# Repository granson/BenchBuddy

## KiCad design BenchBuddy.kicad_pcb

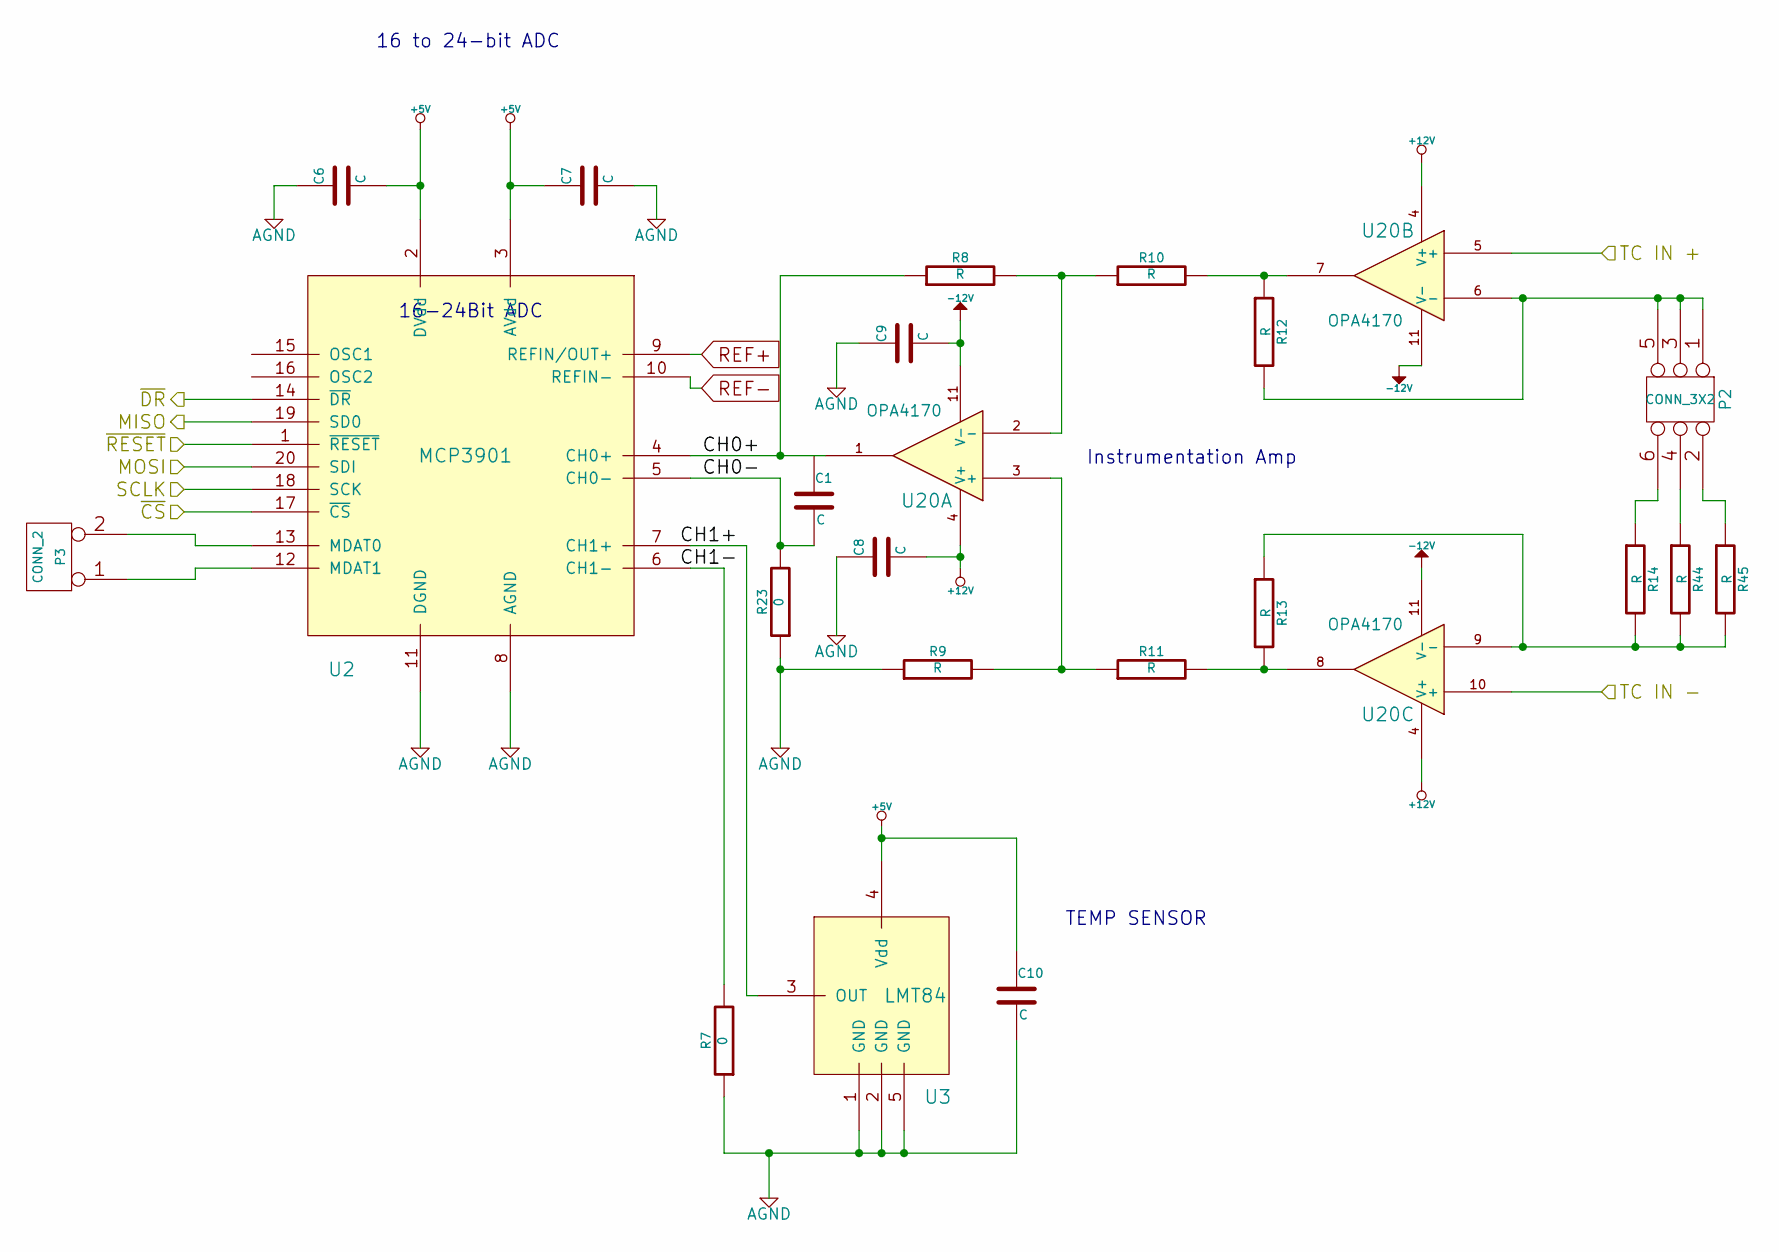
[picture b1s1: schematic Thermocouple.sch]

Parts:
C1, C6, C7, C8, C9, C10: C
P2: CONN_3X2
P3: CONN_2
R7, R23: 0
R8, R9, R10, R11, R12, R13, R14, R44, R45: R
U2: MCP3901
U3: LMT84
U20: OPA4170

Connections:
+5V: C6.2, C7.1, C10.1, U2.2 (DVdd), U2.3 (AVdd), U3.4 (Vdd); also elsewhere on the board
+12V: C8.2, U20.4 (V+); also elsewhere on the board
-12V: C9.2, U20.11 (V-); also elsewhere on the board
/Arduino/MISO: U2.19 (SD0); also elsewhere on the board
/Arduino/MOSI: U2.20 (SDI); also elsewhere on the board
/Arduino/SCLK: U2.18 (SCK); also elsewhere on the board
/Arduino/~ADC_CS: U2.17 (~CS); also elsewhere on the board
/Arduino/~DR: U2.14 (~DR); also elsewhere on the board
/Arduino/~RESET: U2.1 (~RESET); also elsewhere on the board
/Thermocouple/CH0+: R8.1, U2.4 (CH0+), U20.1
/Thermocouple/CH0-: C1.2, R23.2, U2.5 (CH0-)
/Thermocouple/TC IN +: U20.5 (+); also elsewhere on the board
/Thermocouple/TC IN -: U20.10 (+); also elsewhere on the board
AGND: C6.1, C7.2, C8.1, C9.1, C10.2, R7.1, R9.1, R23.1, U2.8 (AGND), U2.11 (DGND), U3.1 (GND), U3.2 (GND), U3.5 (GND); also elsewhere on the board
unnamed: P3.2 (PM), U2.13 (MDAT0)
unnamed: P3.1, U2.12 (MDAT1)
unnamed: P2.1, P2.3, P2.5, R12.2, U20.6 (-)
unnamed: R9.2, R11.1, U20.3 (+)
unnamed: R8.2, R10.1, U20.2 (-)
unnamed: R13.1, R14.2, R44.2, R45.2, U20.9 (-)
unnamed: P2.4, R44.1
unnamed: R7.2, U2.6 (CH1-)
unnamed: R11.2, R13.2, U20.8
unnamed: P2.2, R45.1
unnamed: R10.2, R12.1, U20.7
unnamed: U2.7 (CH1+), U3.3 (OUT)
unnamed: P2.6, R14.1

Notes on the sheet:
TEMP SENSOR
Instrumentation Amp
16-24Bit ADC
16 to 24-bit ADC

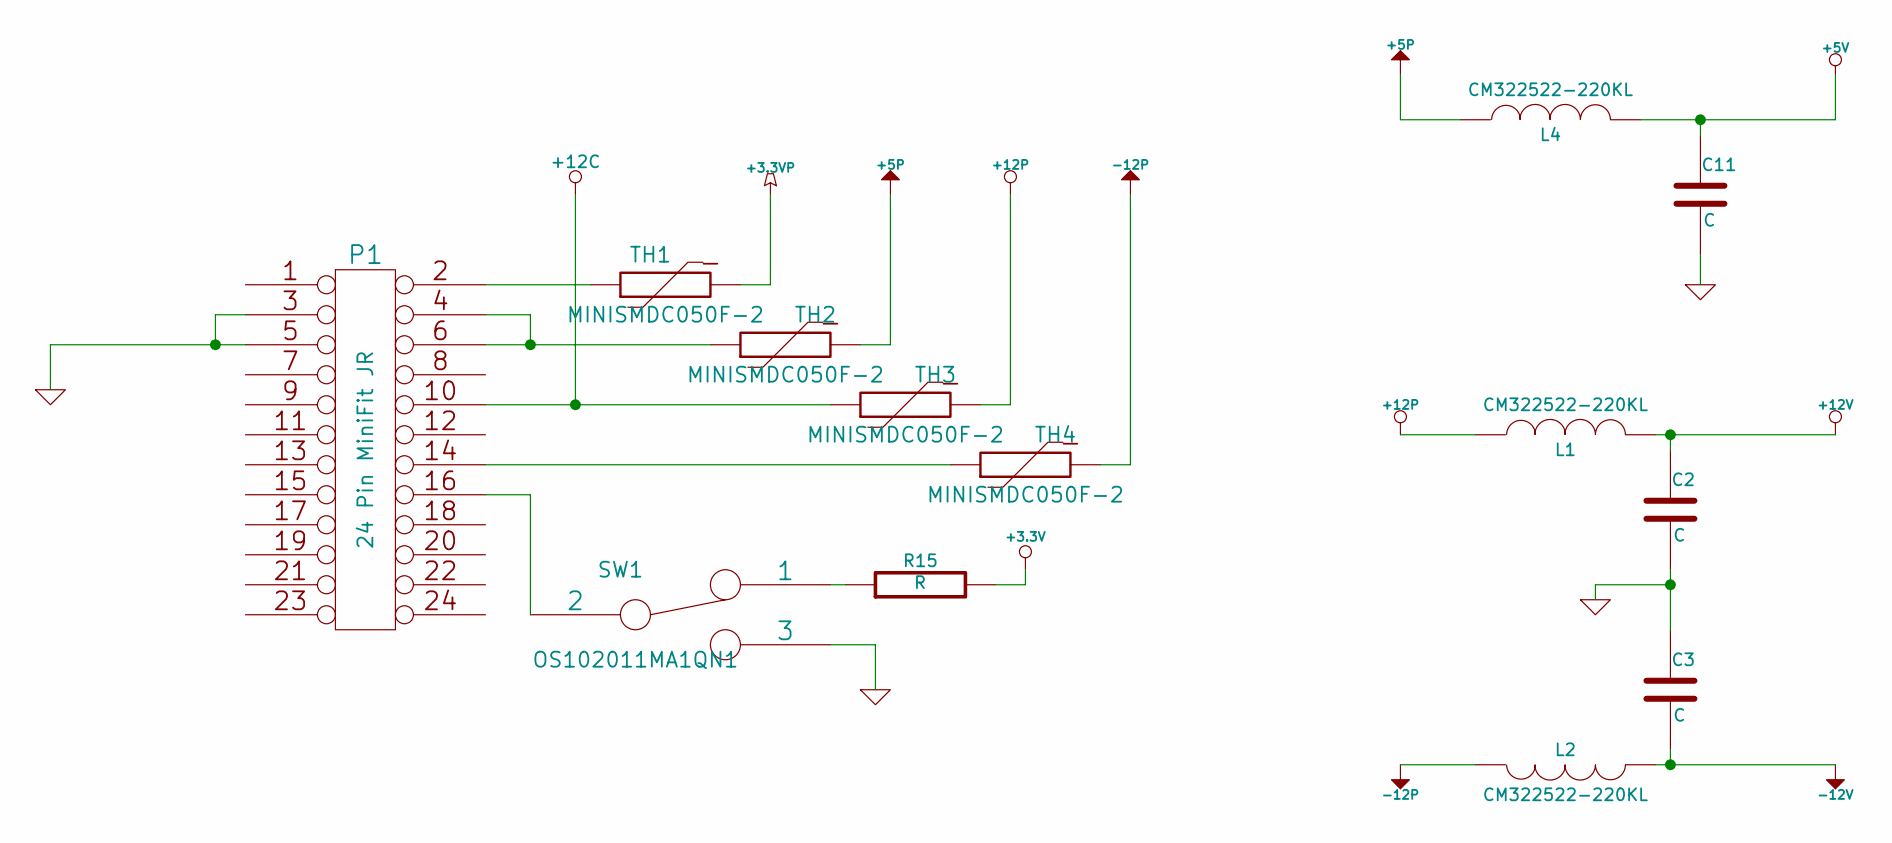
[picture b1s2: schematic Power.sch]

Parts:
C2, C3, C11: C
L1, L2, L4: CM322522-220KL; MFG Part Number CM322522-220KL
P1: 24 Pin MiniFit JR
R15: R
SW1: OS102011MA1QN1; MFG Part Number OS102011MA1QN1
TH1, TH2, TH3, TH4: MINISMDC050F-2; MFG Part Number MINISMDC050F-2

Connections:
+3.3V: R15.2; also elsewhere on the board
+5P: L4.1, TH2.2
+5V: C11.1, L4.2; also elsewhere on the board
+12C: P1.10, TH3.1; also elsewhere on the board
+12P: L1.1, TH3.2; also elsewhere on the board
+12V: C2.1, L1.2; also elsewhere on the board
-12P: L2.1, TH4.2
-12V: C3.2, L2.2; also elsewhere on the board
GND: C2.2, C3.1, C11.2, P1.3, P1.5, SW1.3; also elsewhere on the board
unnamed: R15.1, SW1.1
unnamed: P1.16, SW1.2
unnamed: P1.14, TH4.1
unnamed: P1.2, TH1.1
unnamed: P1.4, P1.6, TH2.1

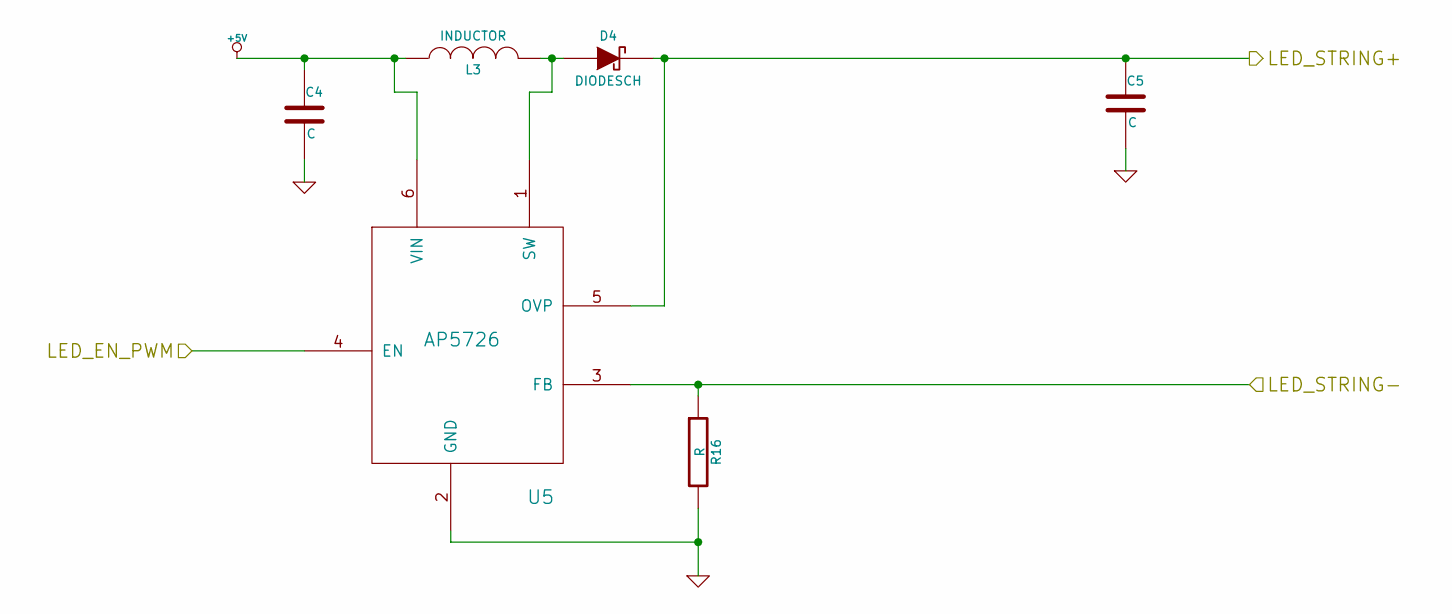
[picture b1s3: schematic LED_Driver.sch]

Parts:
C4, C5: C
D4: DIODESCH
L3: INDUCTOR
R16: R
U5: AP5726

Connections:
+5V: C4.1, L3.1, U5.6 (VIN); also elsewhere on the board
/LED_Driver/LED_STRING+: C5.1, D4.2 (K), U5.5 (OVP); also elsewhere on the board
/LED_Driver/LED_STRING-: R16.1, U5.3 (FB); also elsewhere on the board
GND: C4.2, C5.2, R16.2, U5.2 (GND); also elsewhere on the board
unnamed: D4.1 (A), L3.2, U5.1 (SW)

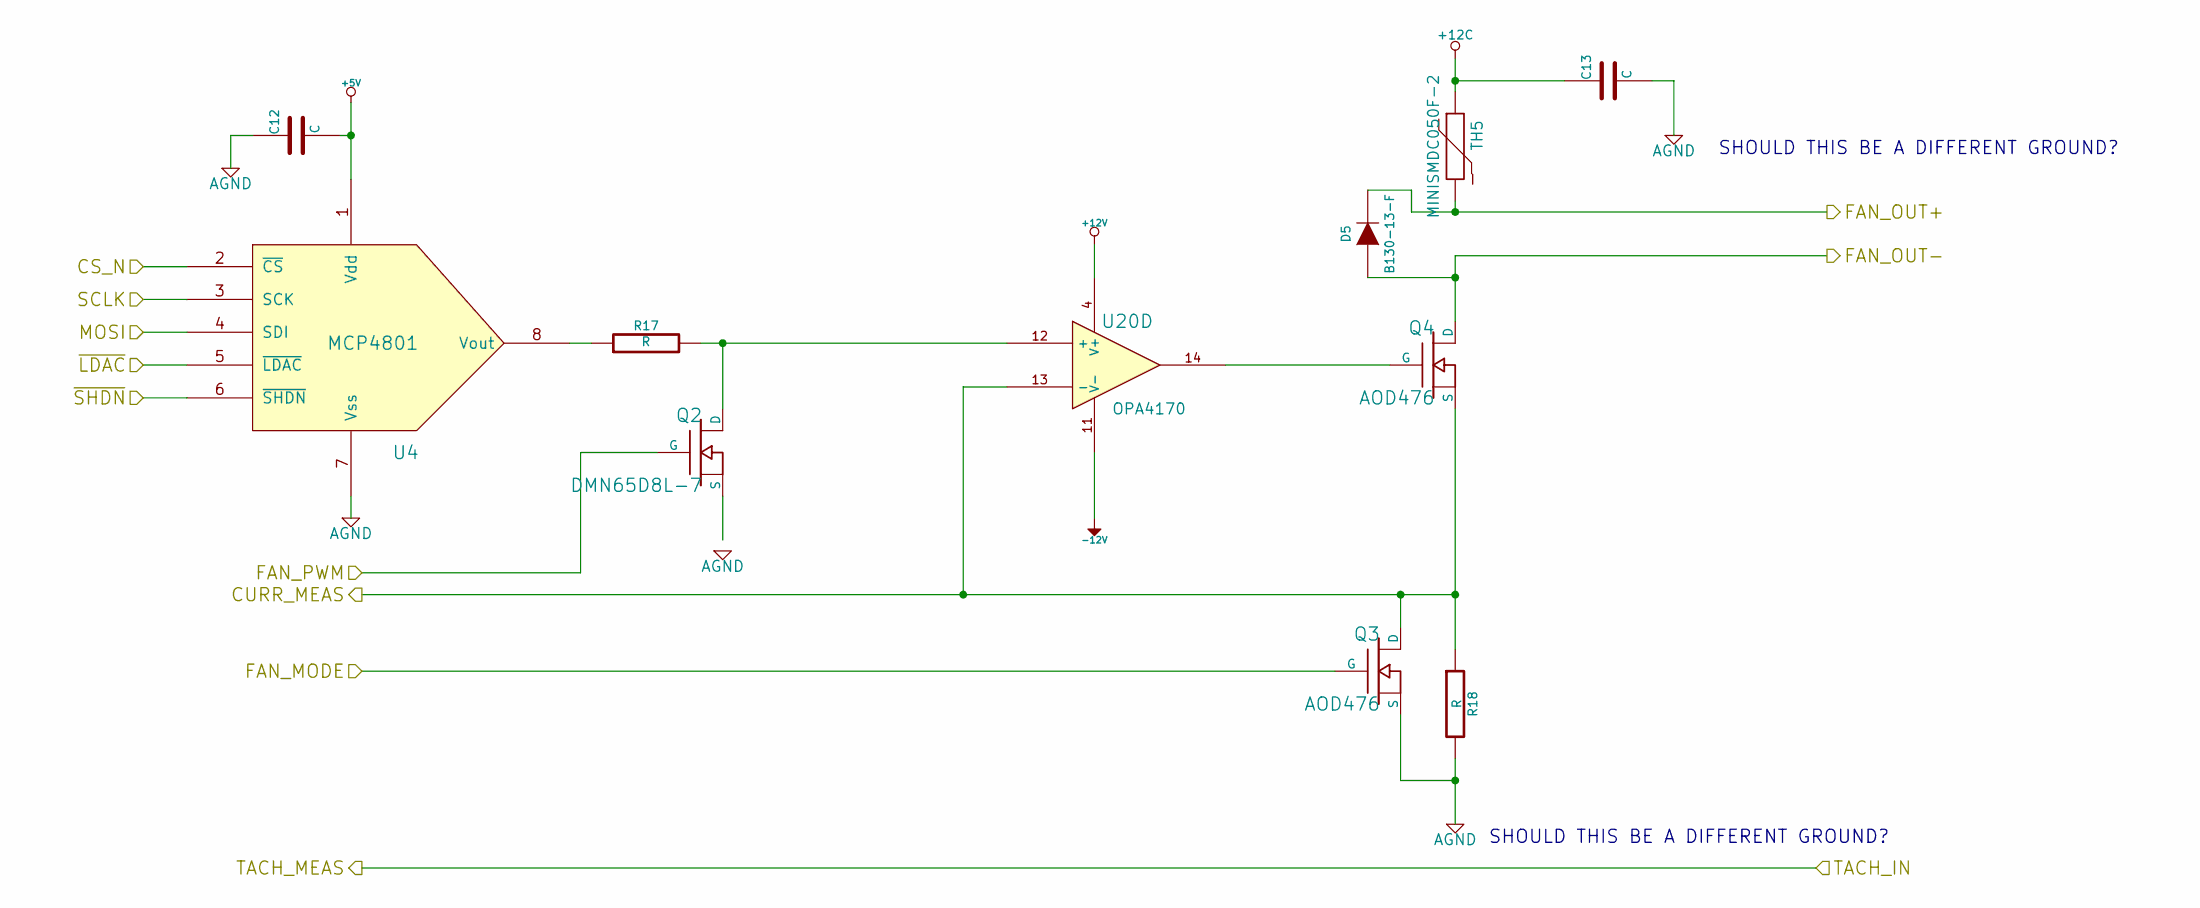
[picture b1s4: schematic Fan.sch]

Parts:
C12, C13: C
D5: B130-13-F; MFG Part Number B130-13-F
Q2: DMN65D8L-7; MFG Part Number DMN65D8L-7
Q3, Q4: AOD476; MFG Part Number AOD476
R17, R18: R
TH5: MINISMDC050F-2; MFG Part Number MINISMDC050F-2
U4: MCP4801
U20: OPA4170

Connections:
+5V: C12.2, U4.1 (Vdd); also elsewhere on the board
+12C: C13.1, TH5.1; also elsewhere on the board
+12V: U20.4 (V+); also elsewhere on the board
-12V: U20.11 (V-); also elsewhere on the board
/Arduino/CURR_MEAS: Q3.2 (D), Q4.3 (S), R18.1, U20.13 (-); also elsewhere on the board
/Arduino/FAN_MODE: Q3.1 (G); also elsewhere on the board
/Arduino/FAN_PWM: Q2.G; also elsewhere on the board
/Arduino/MOSI: U4.4 (SDI); also elsewhere on the board
/Arduino/SCLK: U4.3 (SCK); also elsewhere on the board
/Arduino/~LDAC: U4.5 (~LDAC); also elsewhere on the board
/Arduino/~SHDN: U4.6 (~SHDN); also elsewhere on the board
/Fan/CS_N: U4.2 (~CS); also elsewhere on the board
/Fan/FAN_OUT+: D5.2 (K), TH5.2; also elsewhere on the board
/Fan/FAN_OUT-: D5.1 (A), Q4.2 (D); also elsewhere on the board
AGND: C12.1, C13.2, Q3.3 (S), R18.2, U4.7 (Vss); also elsewhere on the board
unnamed: Q2.2 (D), Q2.D, R17.2, U20.12 (+)
unnamed: R17.1, U4.8 (Vout)
unnamed: Q4.1 (G), U20.14

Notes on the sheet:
SHOULD THIS BE A DIFFERENT GROUND?

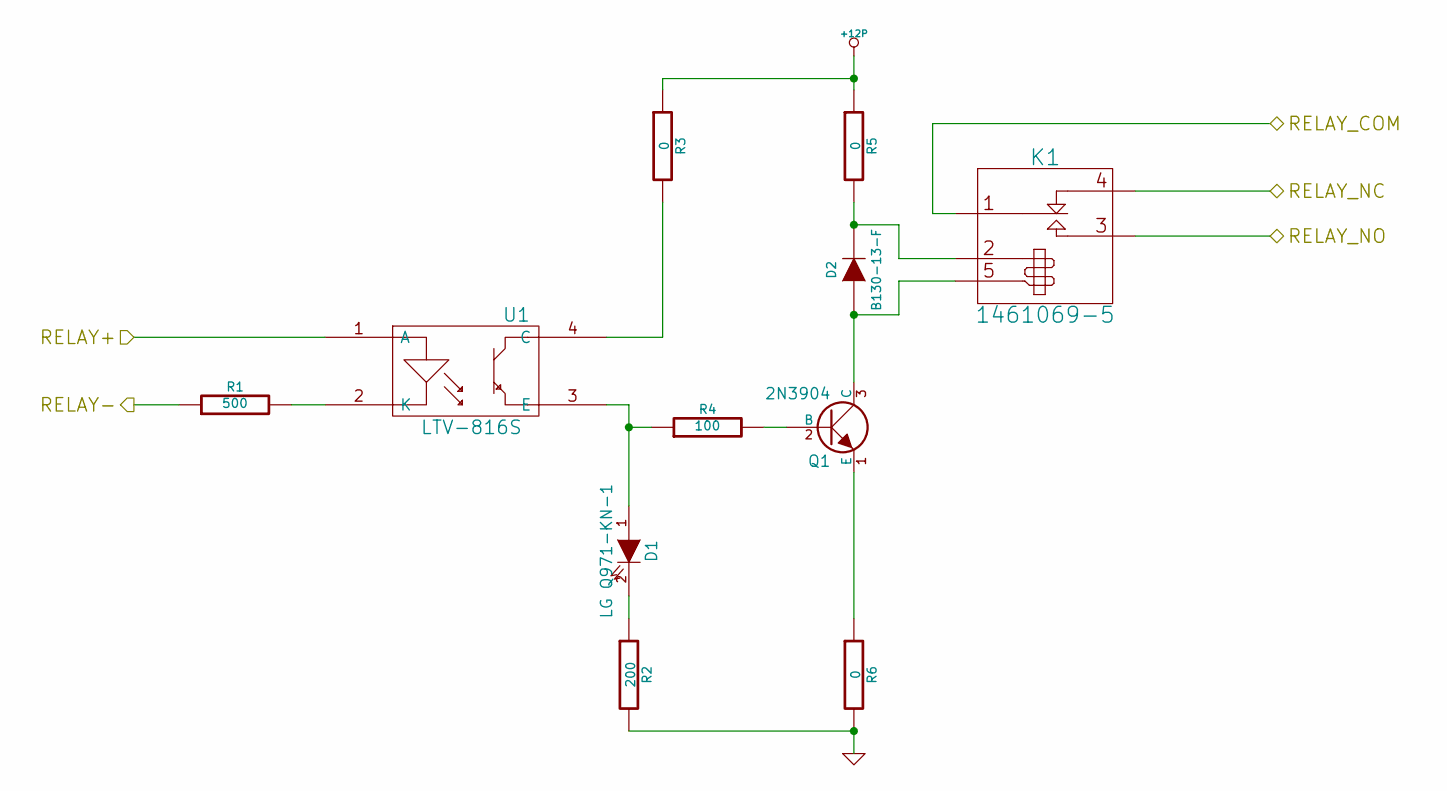
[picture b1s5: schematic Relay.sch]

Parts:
D1: LG Q971-KN-1
D2: B130-13-F
K1: 1461069-5; MFG Part Number 1461069-5
Q1: 2N3904; MFG Part Number MMBT3904-7-F
R1: 500
R2: 200
R3, R5, R6: 0
R4: 100
U1: LTV-816S

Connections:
+12P: R3.1, R5.1; also elsewhere on the board
/Arduino/RELAY+: U1.1 (A); also elsewhere on the board
/Arduino/RELAY-: R1.1; also elsewhere on the board
/Relay/RELAY_COM: K1.1 (COM); also elsewhere on the board
/Relay/RELAY_NC: K1.4 (NC); also elsewhere on the board
/Relay/RELAY_NO: K1.3 (NO); also elsewhere on the board
GND: R2.2, R6.2; also elsewhere on the board
unnamed: D1.2 (K), R2.1
unnamed: Q1.2 (B), R4.2
unnamed: D1.1 (A), R4.1, U1.3 (E)
unnamed: D2.1 (A), K1.5 (COIL-), Q1.3 (C)
unnamed: Q1.1 (E), R6.1
unnamed: R3.2, U1.4 (C)
unnamed: D2.2 (K), K1.2 (COIL+), R5.2
unnamed: R1.2, U1.2 (K)

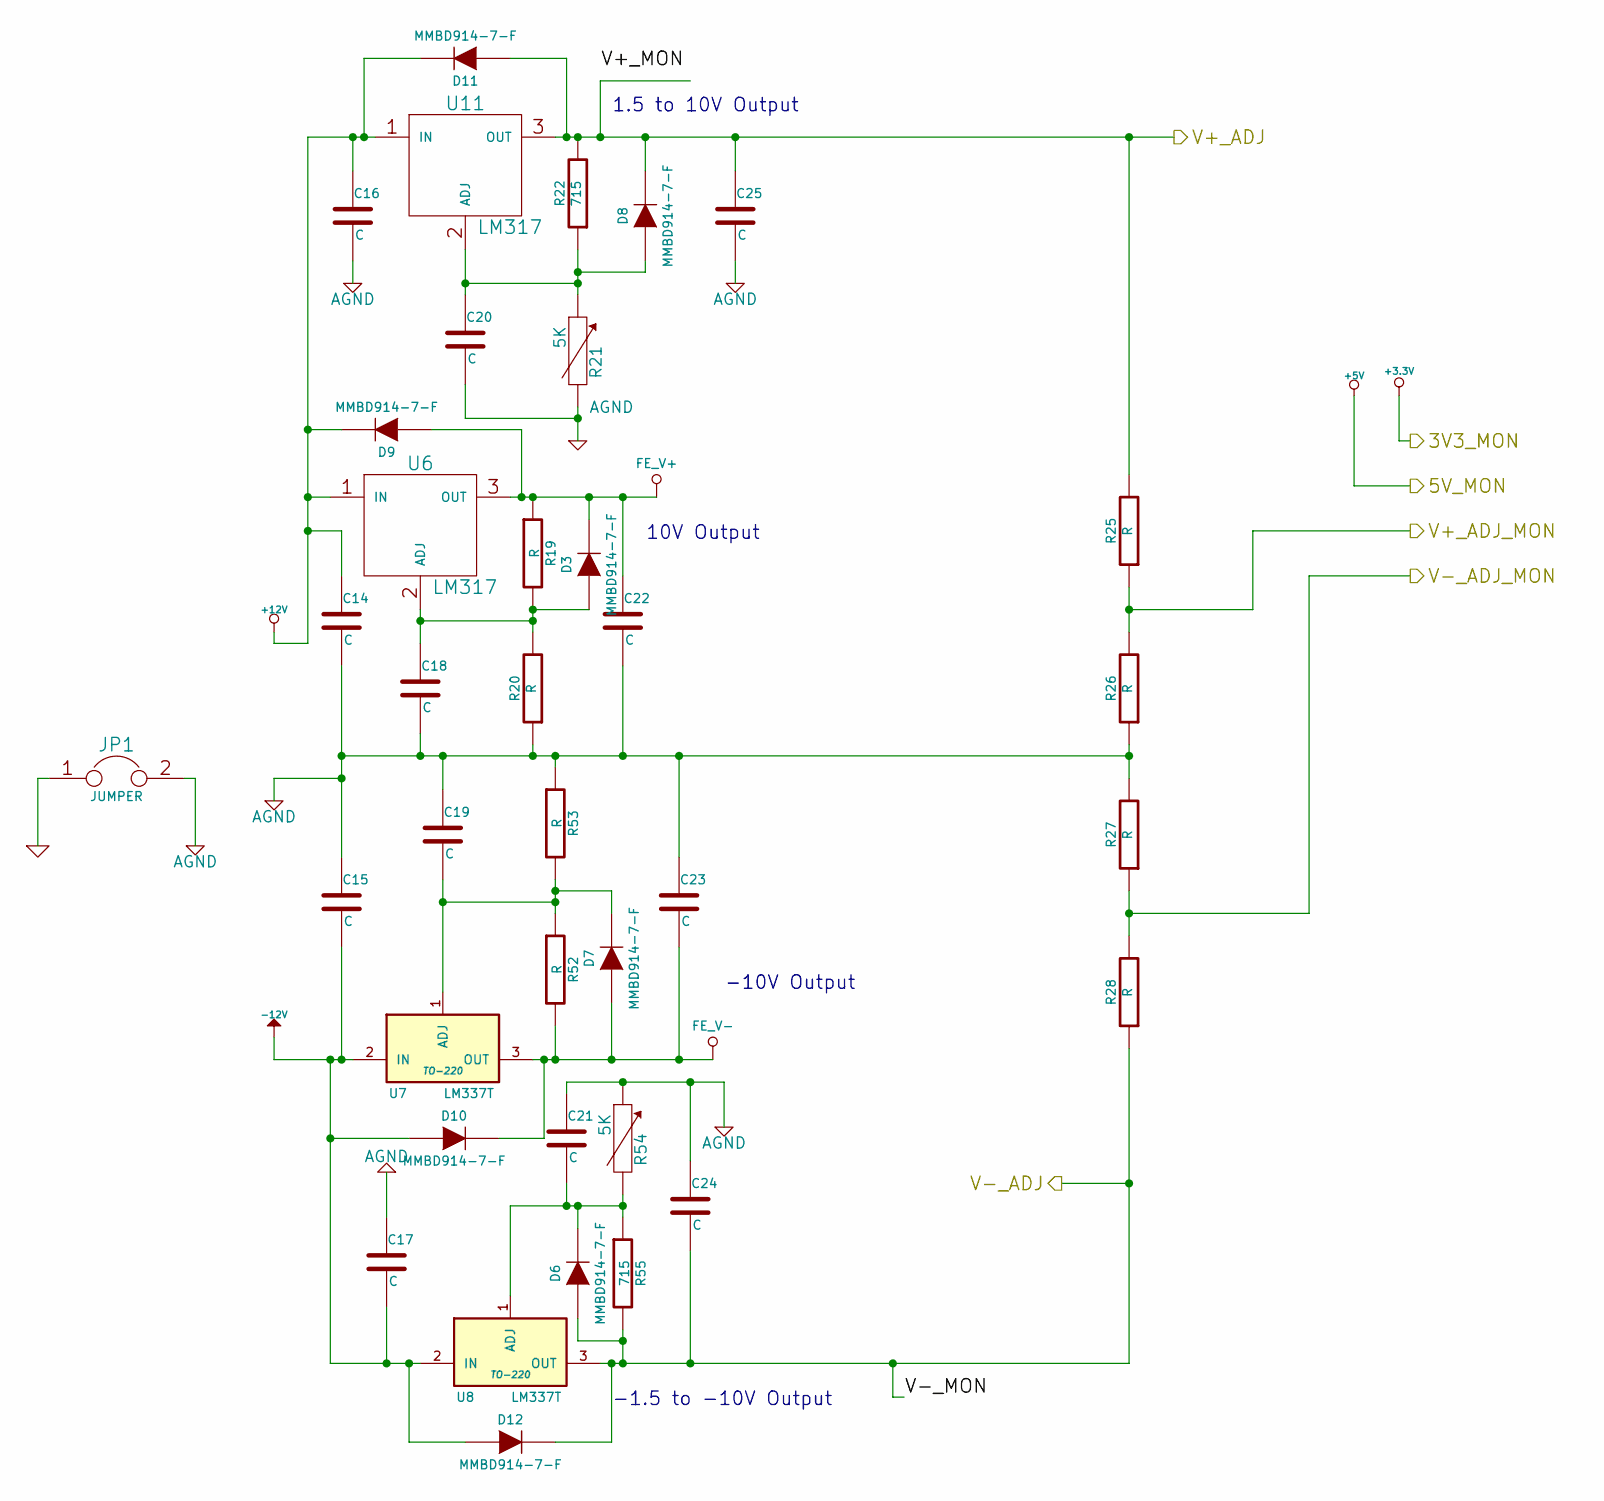
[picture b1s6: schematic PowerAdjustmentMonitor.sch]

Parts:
C14, C15, C16, C17, C18, C19, C20, C21, C22, C23, C24, C25: C
D3, D6, D7, D8, D9, D10, D11, D12: MMBD914-7-F
JP1: JUMPER
R19, R20, R25, R26, R27, R28, R52, R53: R
R21, R54: 5K
R22, R55: 715
U6, U11: LM317
U7, U8: LM337T; TO-220

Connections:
+12V: C14.1, C16.1, D9.2 (K), D11.2 (K), U6.1 (IN), U11.1 (IN); also elsewhere on the board
-12V: C15.2, C17.2, D10.1 (A), D12.1 (A), U7.2 (IN), U8.2 (IN); also elsewhere on the board
/Arduino/V+_ADJ_MON: R25.1, R26.2; also elsewhere on the board
/Arduino/V-_ADJ_MON: R27.1, R28.2; also elsewhere on the board
/PowerAdjustmentMonitor/V+_ADJ: C25.1, D8.2 (K), D11.1 (A), R22.2, R25.2, U11.3 (OUT); also elsewhere on the board
/PowerAdjustmentMonitor/V-_ADJ: C24.2, D6.1 (A), D12.2 (K), R28.1, R55.2, U8.3 (OUT); also elsewhere on the board
AGND: C14.2, C15.1, C16.2, C17.1, C18.2, C19.1, C20.2, C21.1, C22.2, C23.1, C24.1, C25.2, JP1.2, R20.1, R21.2, R26.1, R27.2, R53.1, R54.1; also elsewhere on the board
unnamed: C18.1, D3.1 (A), R19.2, R20.2, U6.2 (ADJ)
unnamed: C20.1, D8.1 (A), R21.1, R22.1, U11.2 (ADJ)
unnamed: C19.2, D7.2 (K), R52.1, R53.2, U7.1 (ADJ)
unnamed: C21.2, D6.2 (K), R54.2, R55.1, U8.1 (ADJ)

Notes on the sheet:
1.5 to 10V Output
10V Output
-1.5 to -10V Output
-10V Output

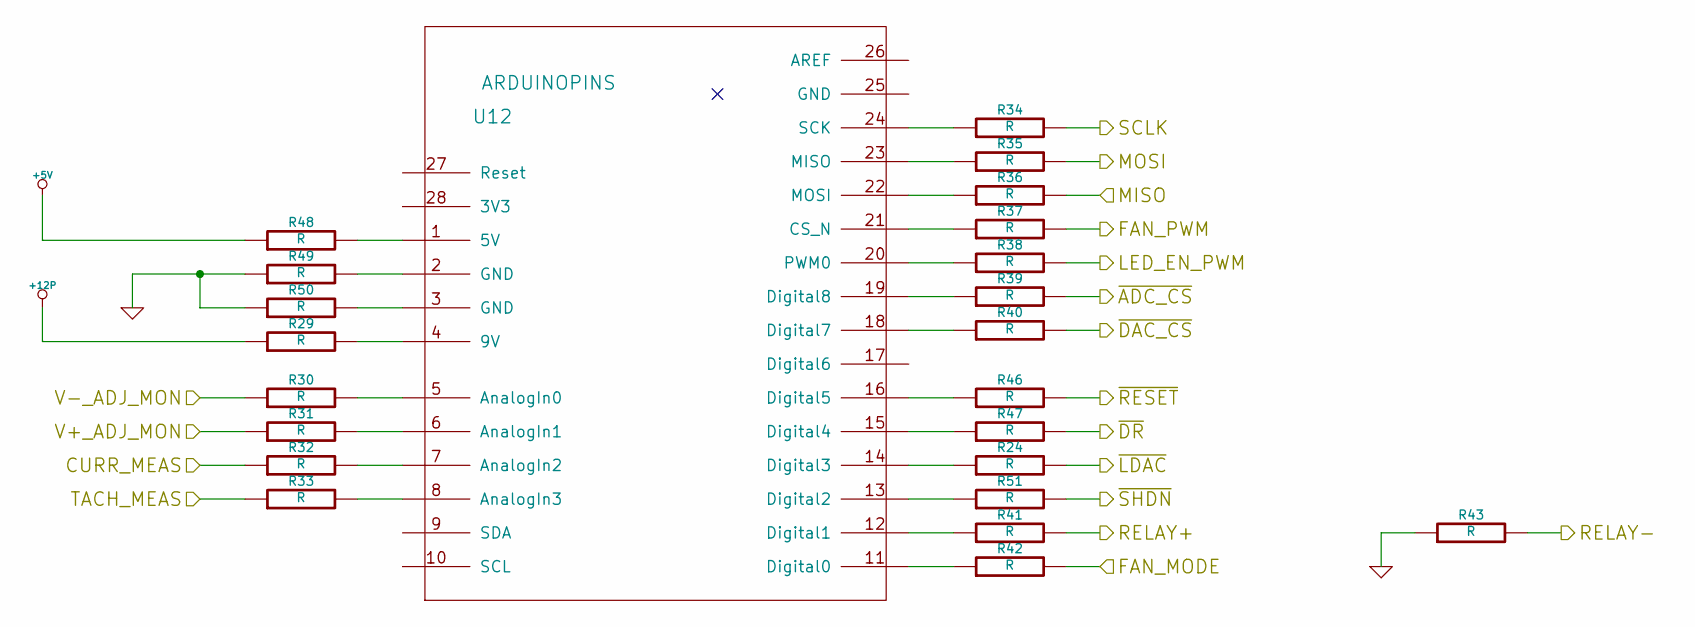
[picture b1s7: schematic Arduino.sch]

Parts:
R24, R29, R30, R31, R32, R33, R34, R35, R36, R37, R38, R39, R40, R41, R42, R43, R46, R47, R48, R49, R50, R51: R
U12: ARDUINOPINS

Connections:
+5V: R48.1; also elsewhere on the board
+12P: R29.1; also elsewhere on the board
/Arduino/CURR_MEAS: R32.1; also elsewhere on the board
/Arduino/FAN_MODE: R42.2; also elsewhere on the board
/Arduino/FAN_PWM: R37.2; also elsewhere on the board
/Arduino/LED_EN_PWM: R38.2
/Arduino/MISO: R36.2; also elsewhere on the board
/Arduino/MOSI: R35.2; also elsewhere on the board
/Arduino/RELAY+: R41.2; also elsewhere on the board
/Arduino/RELAY-: R43.2; also elsewhere on the board
/Arduino/SCLK: R34.2; also elsewhere on the board
/Arduino/V+_ADJ_MON: R31.1; also elsewhere on the board
/Arduino/V-_ADJ_MON: R30.1; also elsewhere on the board
/Arduino/~ADC_CS: R39.2; also elsewhere on the board
/Arduino/~DR: R47.2; also elsewhere on the board
/Arduino/~LDAC: R24.2; also elsewhere on the board
/Arduino/~RESET: R46.2; also elsewhere on the board
/Arduino/~SHDN: R51.2; also elsewhere on the board
/Fan/CS_N: R40.2; also elsewhere on the board
/Fan/TACH_IN: R33.1; also elsewhere on the board
GND: R43.1, R49.1, R50.1; also elsewhere on the board
unnamed: R37.1, U12.21 (CS_N)
unnamed: R33.2, U12.8 (AnalogIn3)
unnamed: R32.2, U12.7 (AnalogIn2)
unnamed: R41.1, U12.12 (Digital1)
unnamed: R31.2, U12.6 (AnalogIn1)
unnamed: R30.2, U12.5 (AnalogIn0)
unnamed: R29.2, U12.4 (9V)
unnamed: R50.2, U12.3 (GND)
unnamed: R49.2, U12.2 (GND)
unnamed: R48.2, U12.1 (5V)
unnamed: R34.1, U12.24 (SCK)
unnamed: R46.1, U12.16 (Digital5)
unnamed: R35.1, U12.23 (MISO)
unnamed: R36.1, U12.22 (MOSI)
unnamed: R42.1, U12.11 (Digital0)
unnamed: R38.1, U12.20 (PWM0)
unnamed: R24.1, U12.14 (Digital3)
unnamed: R51.1, U12.13 (Digital2)
unnamed: R47.1, U12.15 (Digital4)
unnamed: R40.1, U12.18 (Digital7)
unnamed: R39.1, U12.19 (Digital8)

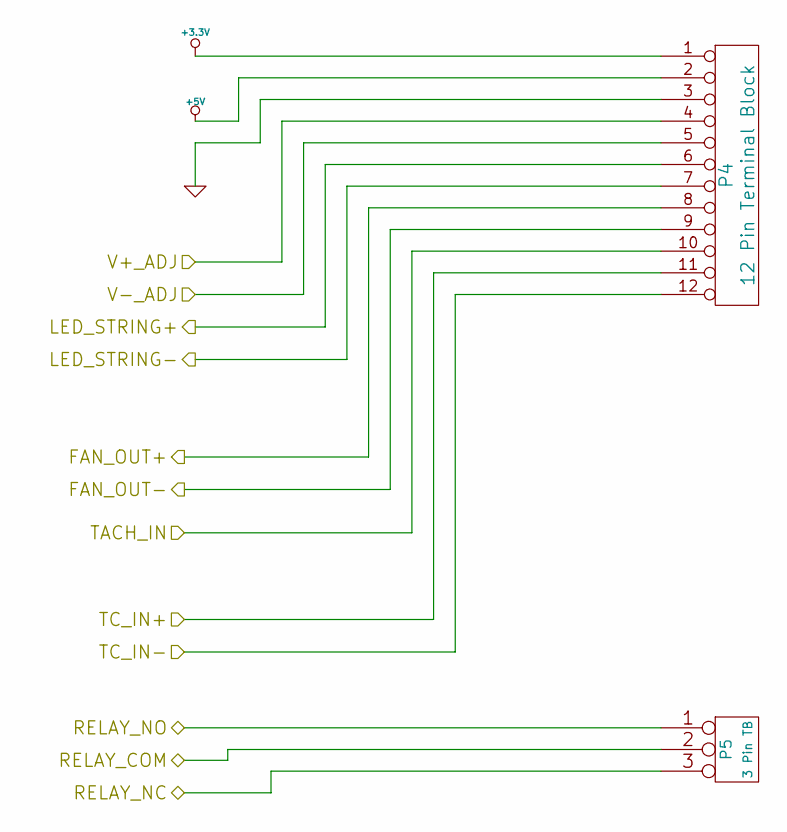
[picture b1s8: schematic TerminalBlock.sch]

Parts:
P4: 12 Pin Terminal Block; MFG Part Number OSTTE120104
P5: 3 Pin TB; MFG Part Number 1935174

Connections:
+3.3V: P4.1; also elsewhere on the board
+5V: P4.2; also elsewhere on the board
/Fan/FAN_OUT+: P4.8; also elsewhere on the board
/Fan/FAN_OUT-: P4.9; also elsewhere on the board
/Fan/TACH_IN: P4.10; also elsewhere on the board
/LED_Driver/LED_STRING+: P4.6; also elsewhere on the board
/LED_Driver/LED_STRING-: P4.7; also elsewhere on the board
/PowerAdjustmentMonitor/V+_ADJ: P4.4; also elsewhere on the board
/PowerAdjustmentMonitor/V-_ADJ: P4.5; also elsewhere on the board
/Relay/RELAY_COM: P5.2 (PM); also elsewhere on the board
/Relay/RELAY_NC: P5.3; also elsewhere on the board
/Relay/RELAY_NO: P5.1; also elsewhere on the board
/Thermocouple/TC IN +: P4.11; also elsewhere on the board
/Thermocouple/TC IN -: P4.12; also elsewhere on the board
GND: P4.3; also elsewhere on the board

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
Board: 4 copper layers, 122 parts (27 on the bottom side), 96 nets, no tracks yet.

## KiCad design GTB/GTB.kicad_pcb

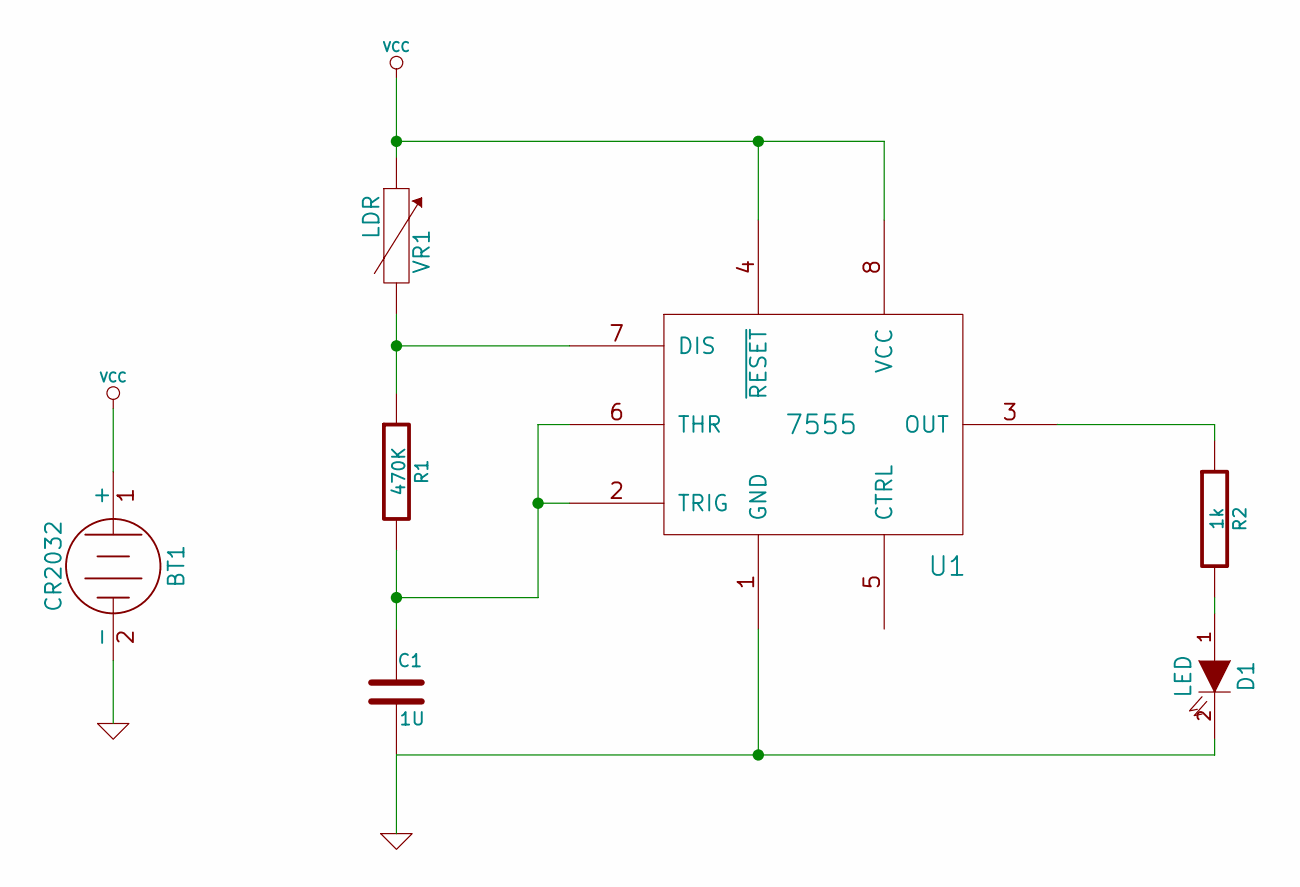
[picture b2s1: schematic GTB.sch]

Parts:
BT1: CR2032
C1: 1U
D1: LED
R1: 470K
R2: 1k
U1: 7555
VR1: LDR

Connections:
GND: BT1.2 (-), C1.2, D1.2 (K), U1.1 (GND)
unnamed: R1.1, U1.7 (DIS), VR1.2
unnamed: D1.1 (A), R2.2
unnamed: R2.1, U1.3 (OUT)
unnamed: C1.1, R1.2, U1.2 (TRIG), U1.6 (THR)
VCC: BT1.1 (+), U1.4 (~RESET), U1.8 (VCC), VR1.1

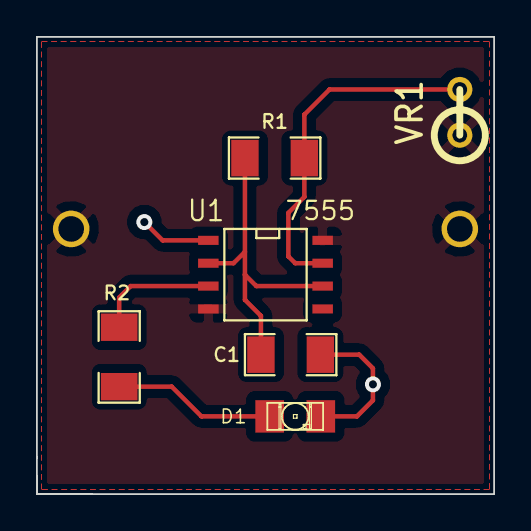
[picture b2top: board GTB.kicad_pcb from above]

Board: 2 copper layers, 25.4 x 25.4 mm, 7 parts (1 on the bottom side), 6 nets.

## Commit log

2013-09-05 As per Project Creation video
2013-09-08 Board Outline (Freeduino used as reference)
2013-09-08 Board Outline (no mounting holes)
2013-09-19 BB with no mounting holes, USB allocation
2013-09-19 Thermocouple Schematic
2013-09-20 Fan Schematic
2013-09-21 Relay Schematic
2013-09-22 Power Protection And Filtering
2013-09-28 Overall Schematic
2013-09-30 Fan/Current Module Refactoring
2013-10-15 Preliminary Module Layouts
2013-10-18 Plug Placement
2013-10-27 Power Modification Module
2013-11-26 November 25 Update
2013-12-02 Power Modification Module (check diodes)
2013-12-03 Power Modification Module - Correct Diode Polarity
